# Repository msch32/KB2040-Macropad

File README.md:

# KB2040-Macropad
Small Macropad to extend a TKL Keyboard with a numbad for blender, etc. Can also be used as a general purpose macropad

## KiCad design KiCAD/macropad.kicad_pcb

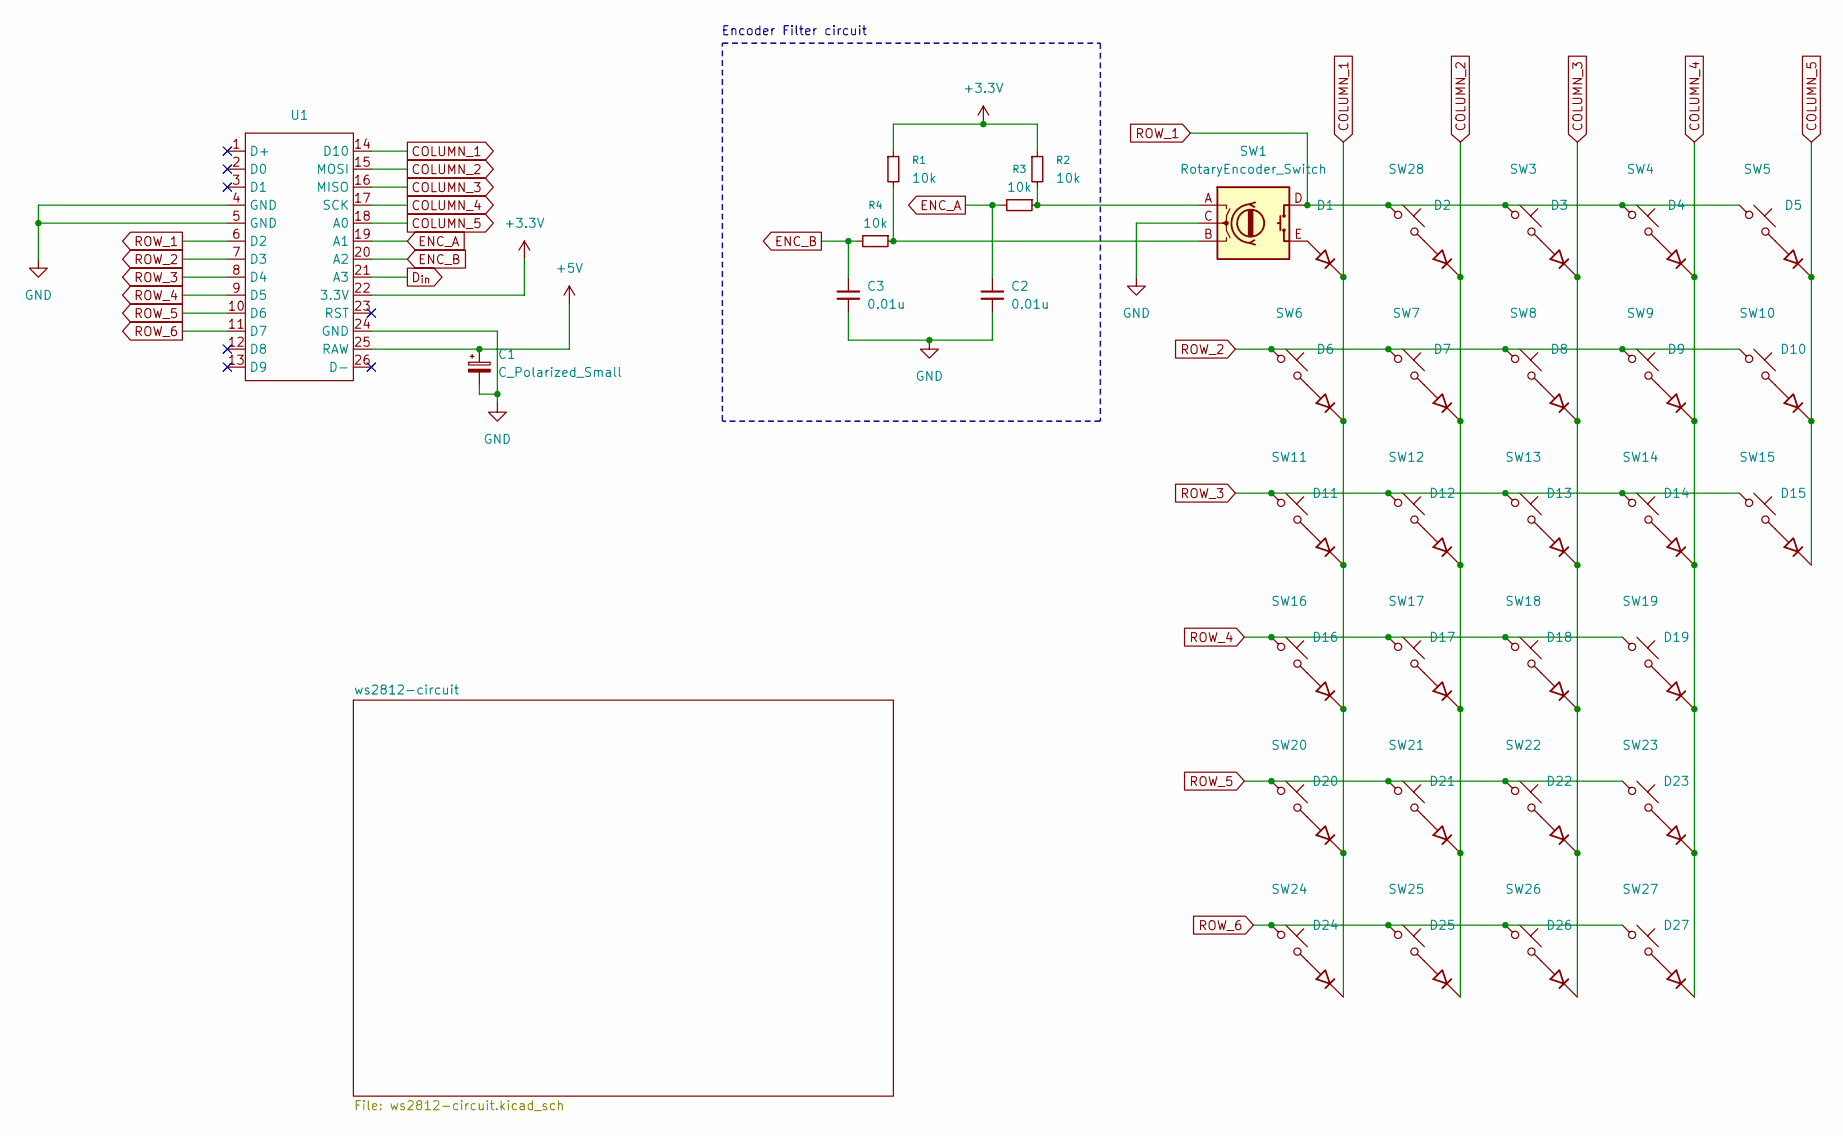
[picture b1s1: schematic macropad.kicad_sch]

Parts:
C1: C_Polarized_Small; CP_Wurth_WCAP-ASLI-D6.3L5.5; Digikey 732-8419-1-ND
C2, C3: 0.01u; C_0603_1608Metric_Pad1.08x0.95mm_HandSolder
D1, D2, D3, D4, D5, D6, D7, D8, D9, D10, D11, D12, D13, D14, D15, D16, D17, D18, D19, D20, D21, D22, D23, D24, D25, D26, D27: 1N4148WS-7-F; D_SOD-323; Digikey 1N4148WS-FDICT-ND
R1, R2, R3, R4: 10k; R_0603_1608Metric_Pad0.98x0.95mm_HandSolder
SW1: RotaryEncoder_Switch; PEC11S-929F-S0015; Digikey 118-PEC11S-929F-S0015-ND
SW3, SW4, SW5, SW6, SW7, SW8, SW9, SW10, SW11, SW12, SW13, SW14, SW16, SW17, SW18, SW19, SW20, SW21, SW22, SW23, SW24, SW26, SW28: SW_Push_45deg; SW_Cherry_MX_PCB_1.00u
SW15, SW27: SW_Push_45deg; SW_Cherry_MX_PCB_2.00u_90deg
SW25: SW_Push_45deg; SW_Cherry_MX_PCB_2.00u
U1: KB2040

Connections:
+3.3V: R1.1, R2.1, U1.22 (3.3V)
+5V: C1.1, U1.25 (RAW); also elsewhere on the board
COLUMN_1: D1.1 (K), D6.1 (K), D11.1 (K), D16.1 (K), D20.1 (K), D24.1 (K), U1.14 (D10)
COLUMN_2: D2.1 (K), D7.1 (K), D12.1 (K), D17.1 (K), D21.1 (K), D25.1 (K), U1.15 (MOSI)
COLUMN_3: D3.1 (K), D8.1 (K), D13.1 (K), D18.1 (K), D22.1 (K), D26.1 (K), U1.16 (MISO)
COLUMN_4: D4.1 (K), D9.1 (K), D14.1 (K), D19.1 (K), D23.1 (K), D27.1 (K), U1.17 (SCK)
COLUMN_5: D5.1 (K), D10.1 (K), D15.1 (K), U1.18 (A0)
D_{in}: U1.21 (A3); also elsewhere on the board
ENC_A: C2.1, R3.2, U1.19 (A1)
ENC_B: C3.1, R4.2, U1.20 (A2)
GND: C1.2, C2.2, C3.2, SW1.C, U1.4 (GND), U1.5 (GND), U1.24 (GND); also elsewhere on the board
unnamed: D1.2 (A), SW1.E
unnamed: D2.2 (A), SW28.2
unnamed: D3.2 (A), SW3.2
unnamed: D4.2 (A), SW4.2
unnamed: D5.2 (A), SW5.2
unnamed: D6.2 (A), SW6.2
unnamed: D7.2 (A), SW7.2
unnamed: D8.2 (A), SW8.2
unnamed: D9.2 (A), SW9.2
unnamed: D10.2 (A), SW10.2
unnamed: D11.2 (A), SW11.2
unnamed: D12.2 (A), SW12.2
unnamed: D13.2 (A), SW13.2
unnamed: D14.2 (A), SW14.2
unnamed: D15.2 (A), SW15.2
unnamed: D16.2 (A), SW16.2
unnamed: D17.2 (A), SW17.2
unnamed: D18.2 (A), SW18.2
unnamed: D19.2 (A), SW19.2
unnamed: D20.2 (A), SW20.2
unnamed: D21.2 (A), SW21.2
unnamed: D22.2 (A), SW22.2
unnamed: D23.2 (A), SW23.2
unnamed: D24.2 (A), SW24.2
unnamed: D25.2 (A), SW25.2
unnamed: D26.2 (A), SW26.2
unnamed: D27.2 (A), SW27.2
unnamed: R1.2, R4.1, SW1.B
unnamed: R2.2, R3.1, SW1.A
ROW_1: SW1.D, SW3.1, SW4.1, SW5.1, SW28.1, U1.6 (D2)
ROW_2: SW6.1, SW7.1, SW8.1, SW9.1, SW10.1, U1.7 (D3)
ROW_3: SW11.1, SW12.1, SW13.1, SW14.1, SW15.1, U1.8 (D4)
ROW_4: SW16.1, SW17.1, SW18.1, SW19.1, U1.9 (D5)
ROW_5: SW20.1, SW21.1, SW22.1, SW23.1, U1.10 (D6)
ROW_6: SW24.1, SW25.1, SW26.1, SW27.1, U1.11 (D7)

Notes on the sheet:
Encoder Filter circuit

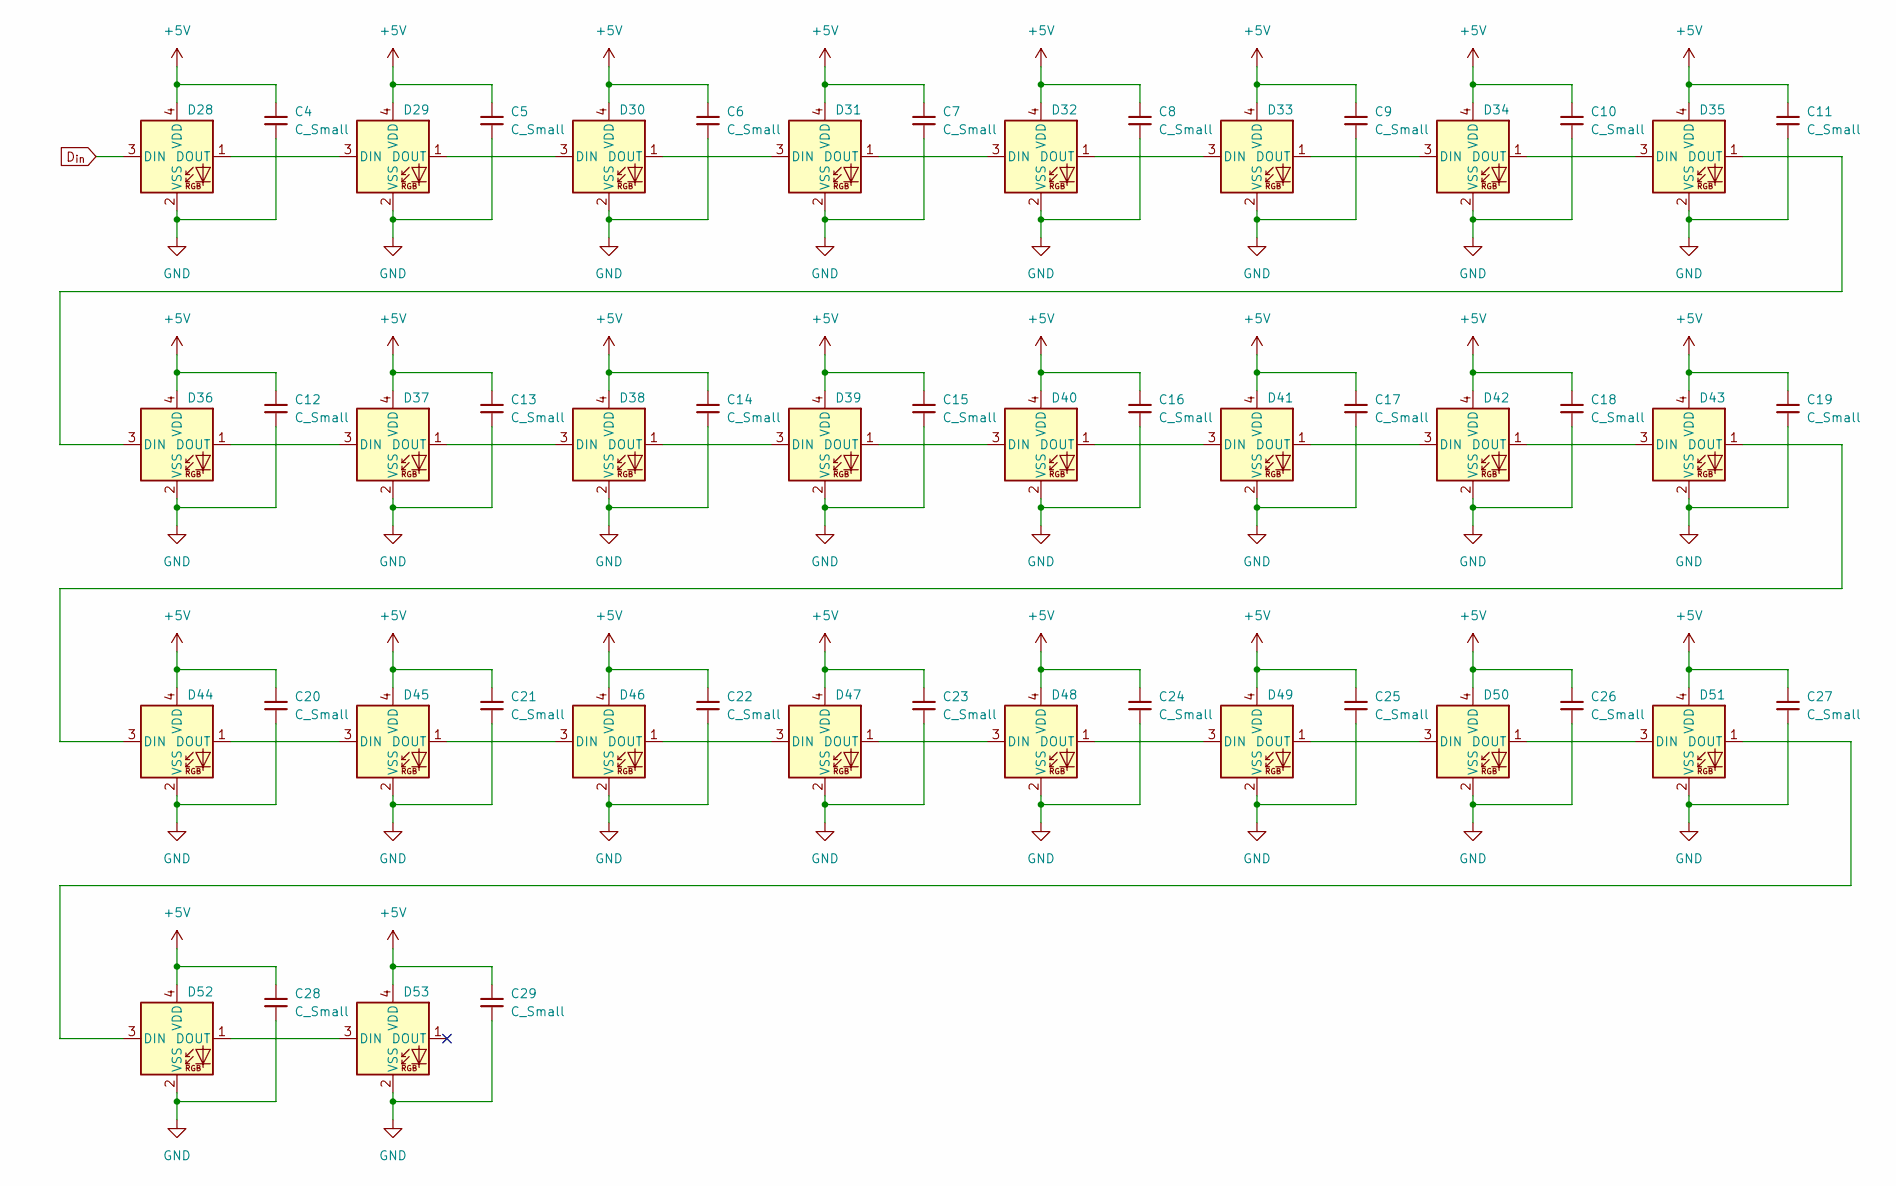
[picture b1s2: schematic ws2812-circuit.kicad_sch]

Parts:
C4, C5, C6, C7, C8, C9, C10, C11, C12, C13, C14, C15, C16, C17, C18, C19, C20, C21, C22, C23, C24, C25, C26, C27, C28, C29: C_Small; C_0603_1608Metric_Pad1.08x0.95mm_HandSolder
D28, D29, D30, D31, D32, D33, D34, D35, D36, D37, D38, D39, D40, D41, D42, D43, D44, D45, D46, D47, D48, D49, D50, D51, D52, D53: WS2812B-2020; adafruit_4960

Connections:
+5V: C4.1, C5.1, C6.1, C7.1, C8.1, C9.1, C10.1, C11.1, C12.1, C13.1, C14.1, C15.1, C16.1, C17.1, C18.1, C19.1, C20.1, C21.1, C22.1, C23.1, C24.1, C25.1, C26.1, C27.1, C28.1, C29.1, D28.4 (VDD), D29.4 (VDD), D30.4 (VDD), D31.4 (VDD), D32.4 (VDD), D33.4 (VDD), D34.4 (VDD), D35.4 (VDD), D36.4 (VDD), D37.4 (VDD), D38.4 (VDD), D39.4 (VDD), D40.4 (VDD), D41.4 (VDD), D42.4 (VDD), D43.4 (VDD), D44.4 (VDD), D45.4 (VDD), D46.4 (VDD), D47.4 (VDD), D48.4 (VDD), D49.4 (VDD), D50.4 (VDD), D51.4 (VDD), D52.4 (VDD), D53.4 (VDD); also elsewhere on the board
D_{in}: D28.3 (DIN); also elsewhere on the board
GND: C4.2, C5.2, C6.2, C7.2, C8.2, C9.2, C10.2, C11.2, C12.2, C13.2, C14.2, C15.2, C16.2, C17.2, C18.2, C19.2, C20.2, C21.2, C22.2, C23.2, C24.2, C25.2, C26.2, C27.2, C28.2, C29.2, D28.2 (VSS), D29.2 (VSS), D30.2 (VSS), D31.2 (VSS), D32.2 (VSS), D33.2 (VSS), D34.2 (VSS), D35.2 (VSS), D36.2 (VSS), D37.2 (VSS), D38.2 (VSS), D39.2 (VSS), D40.2 (VSS), D41.2 (VSS), D42.2 (VSS), D43.2 (VSS), D44.2 (VSS), D45.2 (VSS), D46.2 (VSS), D47.2 (VSS), D48.2 (VSS), D49.2 (VSS), D50.2 (VSS), D51.2 (VSS), D52.2 (VSS), D53.2 (VSS); also elsewhere on the board
unnamed: D28.1 (DOUT), D29.3 (DIN)
unnamed: D29.1 (DOUT), D30.3 (DIN)
unnamed: D30.1 (DOUT), D31.3 (DIN)
unnamed: D31.1 (DOUT), D32.3 (DIN)
unnamed: D32.1 (DOUT), D33.3 (DIN)
unnamed: D33.1 (DOUT), D34.3 (DIN)
unnamed: D34.1 (DOUT), D35.3 (DIN)
unnamed: D35.1 (DOUT), D36.3 (DIN)
unnamed: D36.1 (DOUT), D37.3 (DIN)
unnamed: D37.1 (DOUT), D38.3 (DIN)
unnamed: D38.1 (DOUT), D39.3 (DIN)
unnamed: D39.1 (DOUT), D40.3 (DIN)
unnamed: D40.1 (DOUT), D41.3 (DIN)
unnamed: D41.1 (DOUT), D42.3 (DIN)
unnamed: D42.1 (DOUT), D43.3 (DIN)
unnamed: D43.1 (DOUT), D44.3 (DIN)
unnamed: D44.1 (DOUT), D45.3 (DIN)
unnamed: D45.1 (DOUT), D46.3 (DIN)
unnamed: D46.1 (DOUT), D47.3 (DIN)
unnamed: D47.1 (DOUT), D48.3 (DIN)
unnamed: D48.1 (DOUT), D49.3 (DIN)
unnamed: D49.1 (DOUT), D50.3 (DIN)
unnamed: D50.1 (DOUT), D51.3 (DIN)
unnamed: D51.1 (DOUT), D52.3 (DIN)
unnamed: D52.1 (DOUT), D53.3 (DIN)

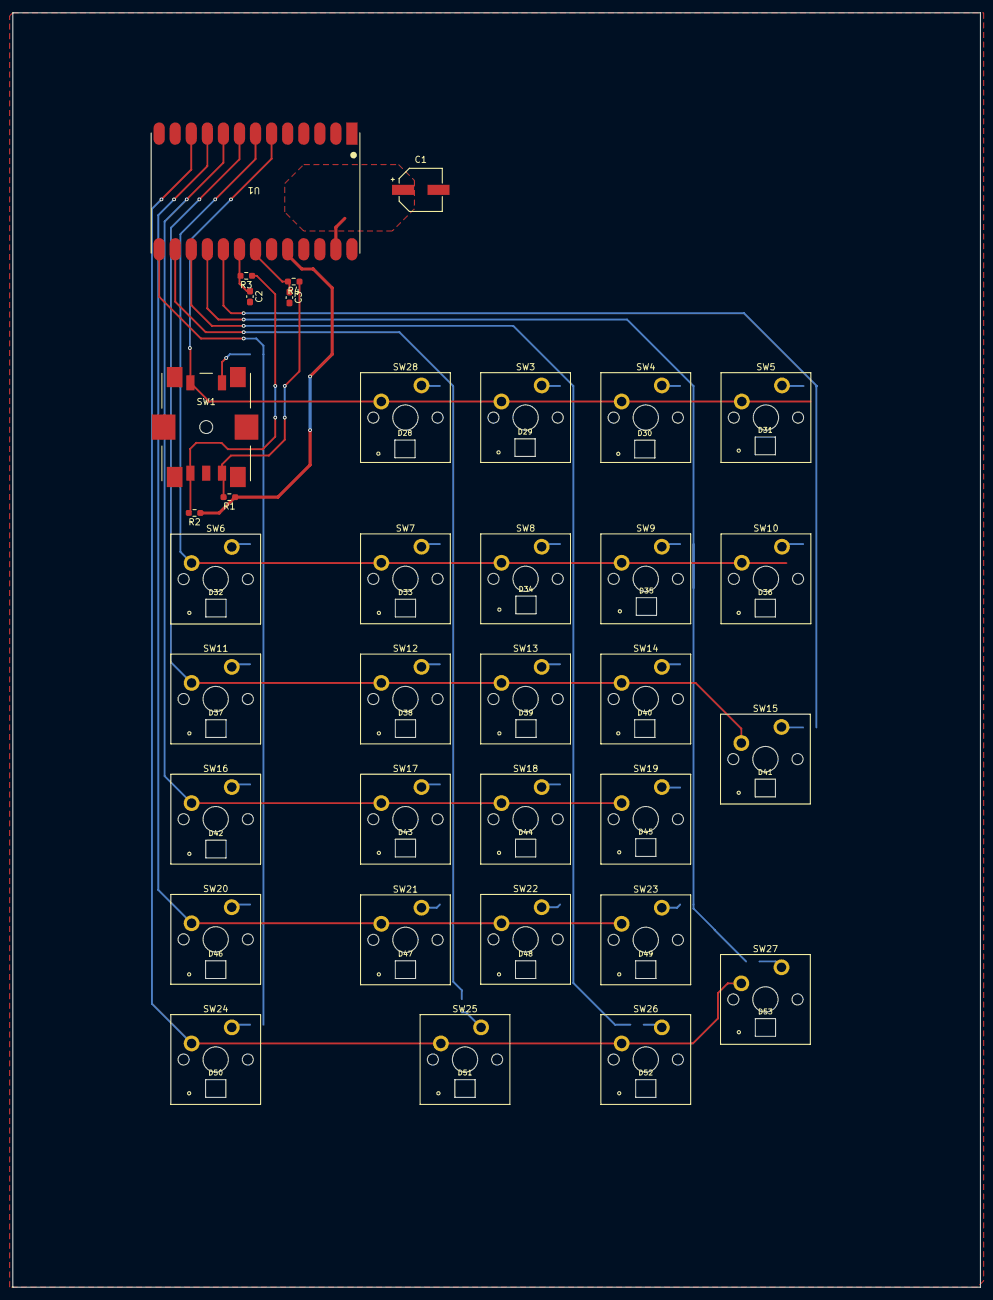
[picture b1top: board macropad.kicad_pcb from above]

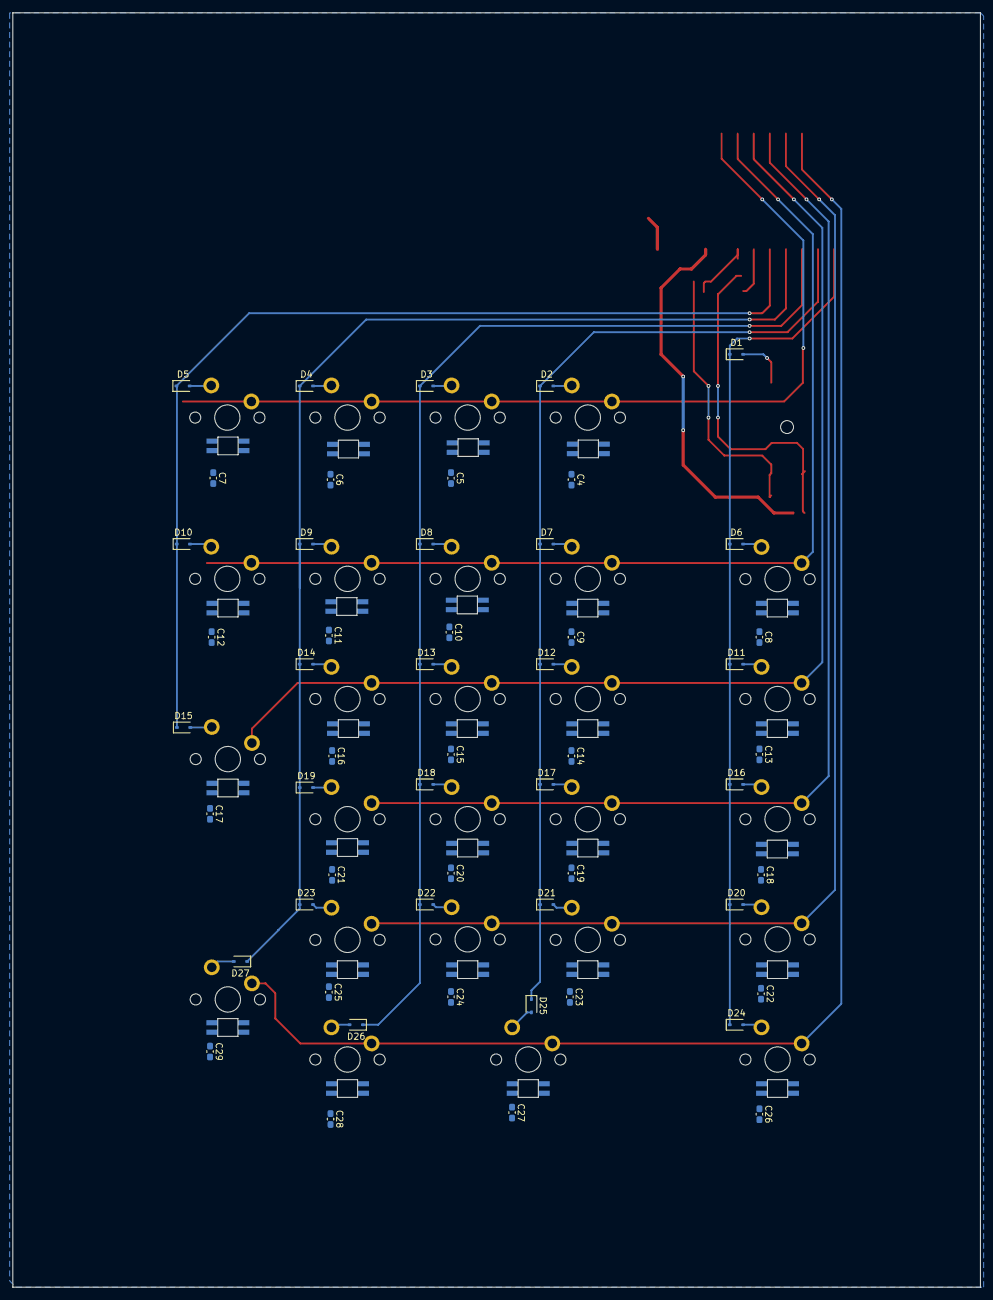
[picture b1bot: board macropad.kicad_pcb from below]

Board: 2 copper layers, 153.0 x 201.5 mm, 114 parts (53 on the bottom side), 71 nets.
